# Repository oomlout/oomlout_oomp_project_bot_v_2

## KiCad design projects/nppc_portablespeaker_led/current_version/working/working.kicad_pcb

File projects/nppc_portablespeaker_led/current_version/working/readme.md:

# portablespeaker
 
## summary 
* id: nppc_portablespeaker_led
* user: nppc
* name: portablespeaker
* board: led
* repo: https://github.com/nppc/PortableSpeaker
* src_file_repo_kicad_pcb: KiCad/Led/Led.kicad_pcb
* src_file_repo_kicad_pcb_link: https://github.com/nppc/PortableSpeaker/tree/master/KiCad/Led/Led.kicad_pcb

* src_file_repo_sch: KiCad/Led/Led.sch
* src_file_repo_sch_link: https://github.com/nppc/PortableSpeaker/tree/master/KiCad/Led/Led.sch
* full details link: https://github.com/oomlout/oomlout_oomp_project_bot_v_2/tree/main/projects/nppc_portablespeaker_led/current_version/working

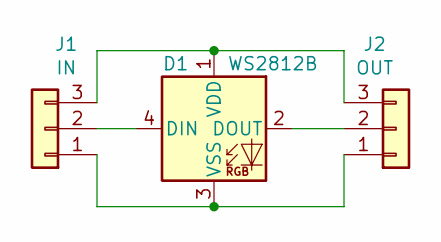
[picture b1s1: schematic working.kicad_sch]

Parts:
D1: WS2812B; LED_WS2812B_PLCC4_5.0x5.0mm_P3.2mm
J1: IN; PinHeader_1x03_P2.54mm_Vertical
J2: OUT; PinHeader_1x03_P2.54mm_Vertical

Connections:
unnamed: D1.1 (VDD), J1.3, J2.3
unnamed: D1.2 (DOUT), J2.2
unnamed: D1.3 (VSS), J1.1, J2.1
unnamed: D1.4 (DIN), J1.2

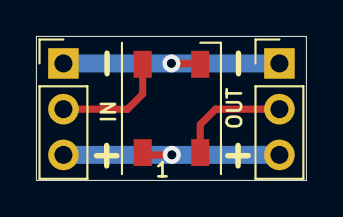
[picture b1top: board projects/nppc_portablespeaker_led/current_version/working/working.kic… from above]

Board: 2 copper layers, 15.0 x 8.0 mm, 3 parts (0 on the bottom side), 4 nets.

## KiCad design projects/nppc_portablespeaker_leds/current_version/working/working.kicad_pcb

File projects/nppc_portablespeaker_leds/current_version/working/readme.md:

# portablespeaker
 
## summary 
* id: nppc_portablespeaker_leds
* user: nppc
* name: portablespeaker
* board: leds
* repo: https://github.com/nppc/PortableSpeaker
* src_file_repo_kicad_pcb: KiCad/Leds/Leds.kicad_pcb
* src_file_repo_kicad_pcb_link: https://github.com/nppc/PortableSpeaker/tree/master/KiCad/Leds/Leds.kicad_pcb

* src_file_repo_sch: KiCad/Leds/Leds.sch
* src_file_repo_sch_link: https://github.com/nppc/PortableSpeaker/tree/master/KiCad/Leds/Leds.sch
* full details link: https://github.com/oomlout/oomlout_oomp_project_bot_v_2/tree/main/projects/nppc_portablespeaker_leds/current_version/working

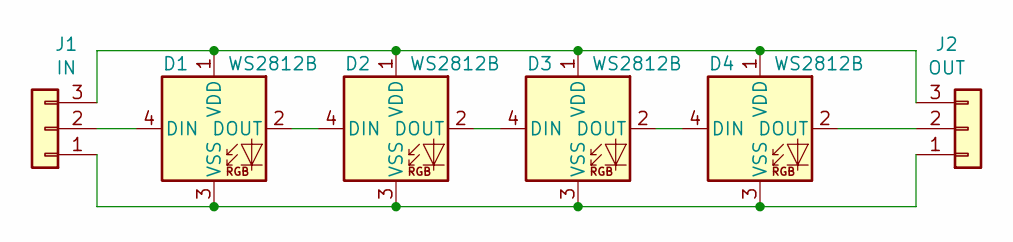
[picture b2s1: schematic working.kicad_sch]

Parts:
D1, D2, D3, D4: WS2812B; LED_WS2812B_PLCC4_5.0x5.0mm_P3.2mm
J1: IN; PinHeader_1x03_P2.54mm_Vertical
J2: OUT; PinHeader_1x03_P2.54mm_Vertical

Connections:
unnamed: D1.1 (VDD), D2.1 (VDD), D3.1 (VDD), D4.1 (VDD), J1.3, J2.3
unnamed: D1.2 (DOUT), D2.4 (DIN)
unnamed: D1.3 (VSS), D2.3 (VSS), D3.3 (VSS), D4.3 (VSS), J1.1, J2.1
unnamed: D1.4 (DIN), J1.2
unnamed: D2.2 (DOUT), D3.4 (DIN)
unnamed: D3.2 (DOUT), D4.4 (DIN)
unnamed: D4.2 (DOUT), J2.2

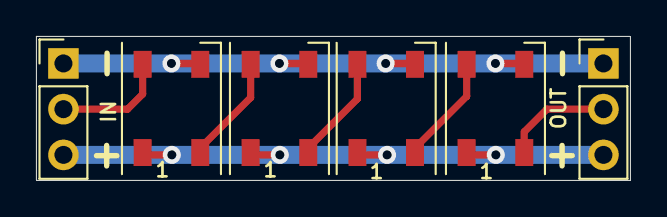
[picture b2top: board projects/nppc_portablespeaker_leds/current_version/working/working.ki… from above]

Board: 2 copper layers, 33.0 x 8.0 mm, 6 parts (0 on the bottom side), 7 nets.

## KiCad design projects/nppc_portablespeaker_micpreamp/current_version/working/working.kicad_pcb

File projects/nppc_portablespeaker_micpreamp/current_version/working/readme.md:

# portablespeaker
 
## summary 
* id: nppc_portablespeaker_micpreamp
* user: nppc
* name: portablespeaker
* board: micpreamp
* repo: https://github.com/nppc/PortableSpeaker
* src_file_repo_kicad_pcb: KiCad/MicPreamp/MicPreamp.kicad_pcb
* src_file_repo_kicad_pcb_link: https://github.com/nppc/PortableSpeaker/tree/master/KiCad/MicPreamp/MicPreamp.kicad_pcb

* src_file_repo_sch: KiCad/MicPreamp/MicPreamp.sch
* src_file_repo_sch_link: https://github.com/nppc/PortableSpeaker/tree/master/KiCad/MicPreamp/MicPreamp.sch
* full details link: https://github.com/oomlout/oomlout_oomp_project_bot_v_2/tree/main/projects/nppc_portablespeaker_micpreamp/current_version/working

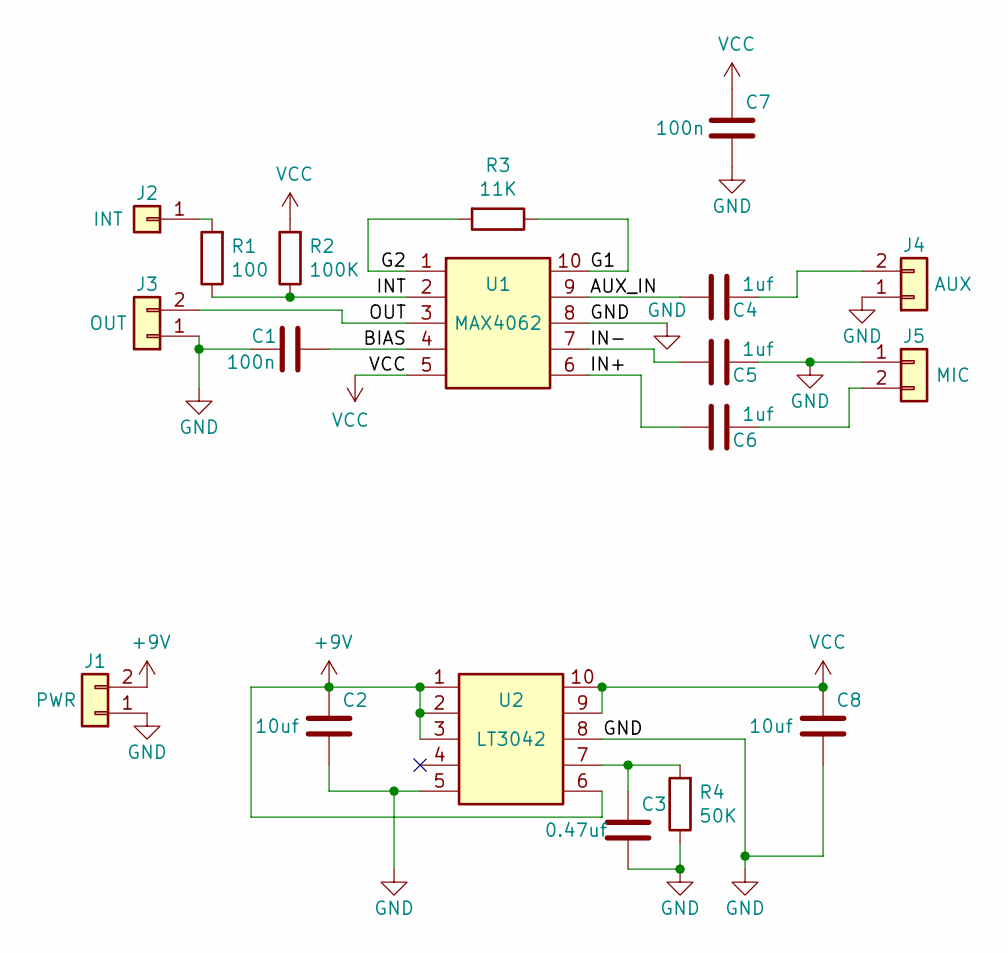
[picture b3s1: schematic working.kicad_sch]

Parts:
C1, C7: 100n; C_0603
C2, C8: 10uf; C_0603
C3: 0.47uf; C_0603
C4, C5, C6: 1uf; C_0603
J1: PWR; Conn_1x02_2.54mm
J2: INT; Conn_1x01_2.54mm
J3: OUT; Conn_1x02_2.54mm
J4: AUX; Conn_1x02_2.54mm
J5: MIC; Conn_1x02_2.54mm
R1: 100; R_0603
R2: 100K; R_0603
R3: 11K; R_0603
R4: 50K; R_0603
U1: MAX4062; TSSOP-10_3x3mm_Pitch0.5mm
U2: LT3042; MSOP-10-1EP_3x3mm_Pitch0.5mm

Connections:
+9V: C2.1, J1.2, U2.1, U2.2, U2.3, U2.6
/AUX_IN: C4.2, U1.9
/BIAS: C1.2, U1.4
/G1: R3.1, U1.10
/G2: R3.2, U1.1
/IN+: C6.2, U1.6
/IN-: C5.2, U1.7
/INT: R1.1, R2.1, U1.2
/OUT: J3.2, U1.3
GND: C1.1, C2.2, C3.2, C5.1, C7.2, C8.2, J1.1, J3.1, J4.1, J5.1, R4.1, U1.8, U2.5, U2.8, U2.11
unnamed: C3.1, R4.2, U2.7
unnamed: C4.1, J4.2
unnamed: C6.1, J5.2
unnamed: J2.1, R1.2
VCC: C7.1, C8.1, R2.2, U1.5, U2.9, U2.10

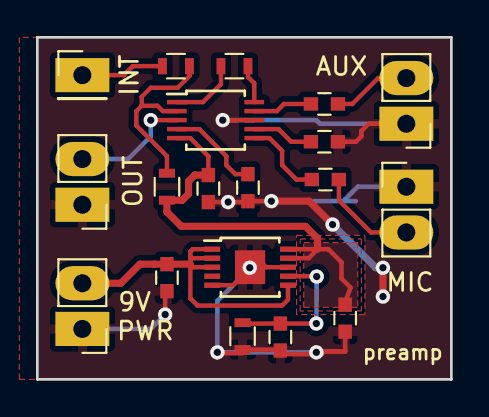
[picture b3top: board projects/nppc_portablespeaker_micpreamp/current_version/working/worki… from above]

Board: 2 copper layers, 23.0 x 19.0 mm, 19 parts (0 on the bottom side), 15 nets.

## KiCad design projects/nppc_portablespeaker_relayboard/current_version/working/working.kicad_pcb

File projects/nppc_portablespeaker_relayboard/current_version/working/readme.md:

# portablespeaker
 
## summary 
* id: nppc_portablespeaker_relayboard
* user: nppc
* name: portablespeaker
* board: relayboard
* repo: https://github.com/nppc/PortableSpeaker
* src_file_repo_kicad_pcb: KiCad/RelayBoard/RelayBoard.kicad_pcb
* src_file_repo_kicad_pcb_link: https://github.com/nppc/PortableSpeaker/tree/master/KiCad/RelayBoard/RelayBoard.kicad_pcb

* src_file_repo_sch: KiCad/RelayBoard/RelayBoard.sch
* src_file_repo_sch_link: https://github.com/nppc/PortableSpeaker/tree/master/KiCad/RelayBoard/RelayBoard.sch
* full details link: https://github.com/oomlout/oomlout_oomp_project_bot_v_2/tree/main/projects/nppc_portablespeaker_relayboard/current_version/working

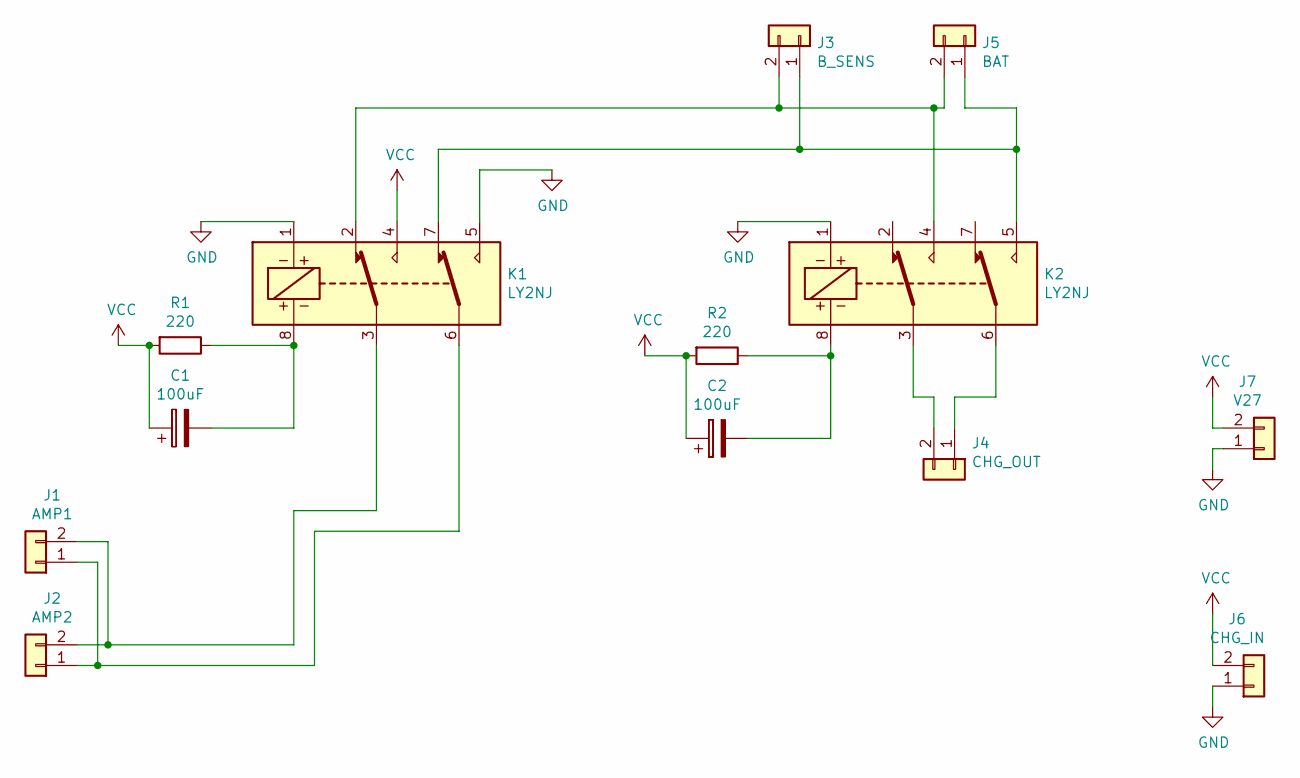
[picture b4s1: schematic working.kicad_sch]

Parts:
C1, C2: 100uF; CP_Radial_D8.0mm_P3.50mm
J1: AMP1; Conn_Power
J2: AMP2; Conn_Power
J3: B_SENS; Conn_1x02_2.54mm
J4: CHG_OUT; Conn_Power
J5: BAT; Conn_Power
J6: CHG_IN; Conn_Power
J7: V27; Conn_Power
K1, K2: LY2NJ; Relay_LY2NJ
R1, R2: 220; R_Axial_DIN0414_L11.9mm_D4.5mm_P20.32mm_Horizontal

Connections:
GND: J6.1, J7.1, K1.1, K1.5, K2.1
unnamed: C1.2, K1.8, R1.1
unnamed: C2.2, K2.8, R2.1
unnamed: J1.1, J2.1, K1.6
unnamed: J1.2, J2.2, K1.3
unnamed 5: J3.1, J5.1, K1.7, K2.5; also elsewhere on the board
unnamed 6: J3.2, J5.2, K1.2, K2.4; also elsewhere on the board
unnamed: J4.1, K2.6
unnamed: J4.2, K2.3
VCC: C1.1, C2.1, J6.2, J7.2, K1.4, R1.2, R2.2

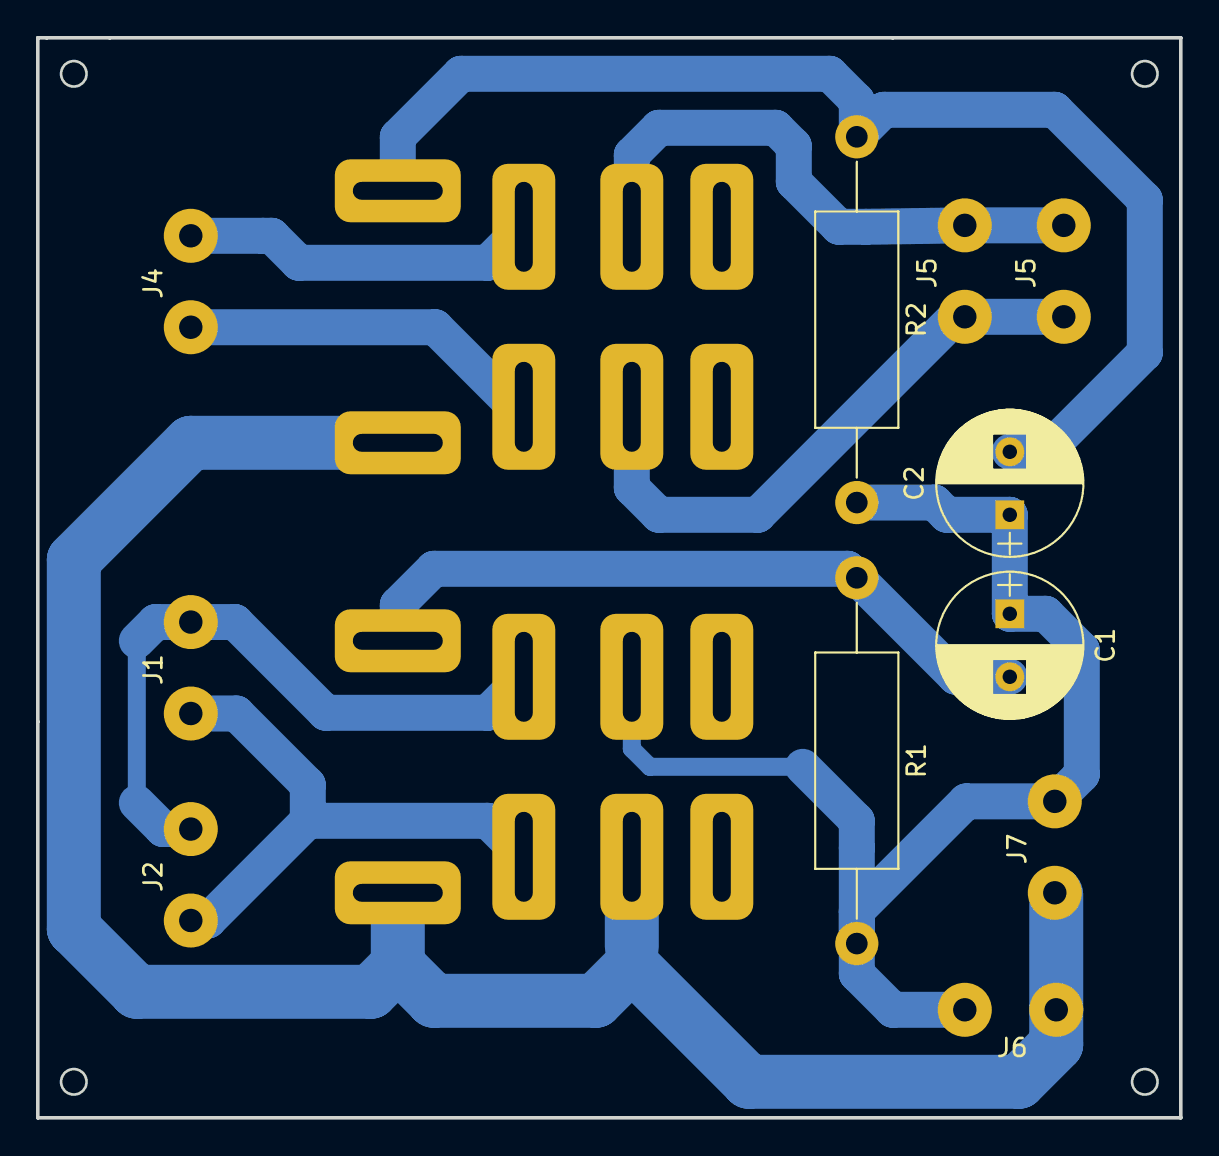
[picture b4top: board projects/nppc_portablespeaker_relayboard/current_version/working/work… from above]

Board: 2 copper layers, 63.5 x 60.0 mm, 13 parts (0 on the bottom side), 10 nets.

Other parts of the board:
J5#2: BAT; Conn_Power

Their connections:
unnamed 5: J5#2.1; also elsewhere on the board
unnamed 6: J5#2.2; also elsewhere on the board

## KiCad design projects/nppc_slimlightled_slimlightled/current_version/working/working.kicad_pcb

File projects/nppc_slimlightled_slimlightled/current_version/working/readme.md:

# slimlightled
 
## summary 
* id: nppc_slimlightled_slimlightled
* user: nppc
* name: slimlightled
* board: slimlightled
* repo: https://github.com/nppc/SlimLightLED
* src_file_repo_kicad_pcb: SlimLightLED.kicad_pcb
* src_file_repo_kicad_pcb_link: https://github.com/nppc/SlimLightLED/tree/master/SlimLightLED.kicad_pcb

* src_file_repo_sch: SlimLightLED.sch
* src_file_repo_sch_link: https://github.com/nppc/SlimLightLED/tree/master/SlimLightLED.sch
* full details link: https://github.com/oomlout/oomlout_oomp_project_bot_v_2/tree/main/projects/nppc_slimlightled_slimlightled/current_version/working

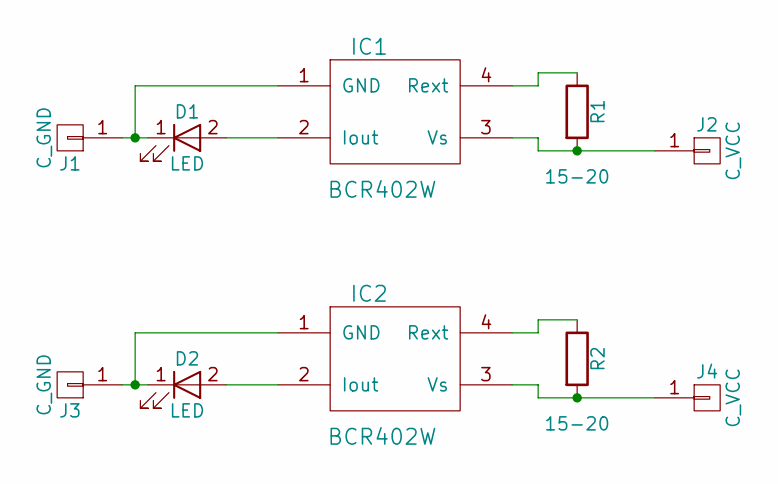
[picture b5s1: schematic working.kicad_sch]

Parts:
D1, D2: LED; 5730
IC1, IC2: BCR402W; BCR402
J1, J3: C_GND; Light_PAD
J2, J4: C_VCC; Light_PAD
R1, R2: 15-20; R_0402_NoSilk

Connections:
unnamed: D1.1 (K), IC1.1 (GND), J1.1
unnamed: D1.2 (A), IC1.2 (Iout)
unnamed: D2.1 (K), IC2.1 (GND), J3.1
unnamed: D2.2 (A), IC2.2 (Iout)
unnamed: IC1.3 (Vs), J2.1, R1.2
unnamed: IC1.4 (Rext), R1.1
unnamed: IC2.3 (Vs), J4.1, R2.2
unnamed: IC2.4 (Rext), R2.1

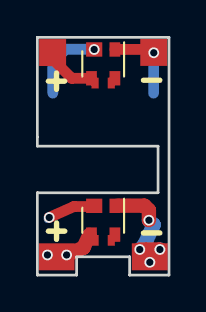
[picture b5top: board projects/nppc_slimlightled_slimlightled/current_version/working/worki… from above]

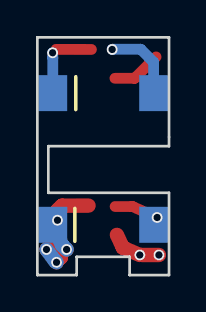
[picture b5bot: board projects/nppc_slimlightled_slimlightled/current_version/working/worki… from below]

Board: 2 copper layers, 7.3 x 13.2 mm, 10 parts (2 on the bottom side), 8 nets.

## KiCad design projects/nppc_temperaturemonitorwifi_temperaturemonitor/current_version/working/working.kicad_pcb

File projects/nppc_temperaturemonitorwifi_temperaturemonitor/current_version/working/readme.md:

# temperaturemonitorwifi
 
## summary 
* id: nppc_temperaturemonitorwifi_temperaturemonitor
* user: nppc
* name: temperaturemonitorwifi
* board: temperaturemonitor
* repo: https://github.com/nppc/TemperatureMonitorWIFI
* src_file_repo_kicad_pcb: KiCad/TemperatureMonitor.kicad_pcb
* src_file_repo_kicad_pcb_link: https://github.com/nppc/TemperatureMonitorWIFI/tree/master/KiCad/TemperatureMonitor.kicad_pcb

* src_file_repo_sch: KiCad/TemperatureMonitor.sch
* src_file_repo_sch_link: https://github.com/nppc/TemperatureMonitorWIFI/tree/master/KiCad/TemperatureMonitor.sch
* full details link: https://github.com/oomlout/oomlout_oomp_project_bot_v_2/tree/main/projects/nppc_temperaturemonitorwifi_temperaturemonitor/current_version/working

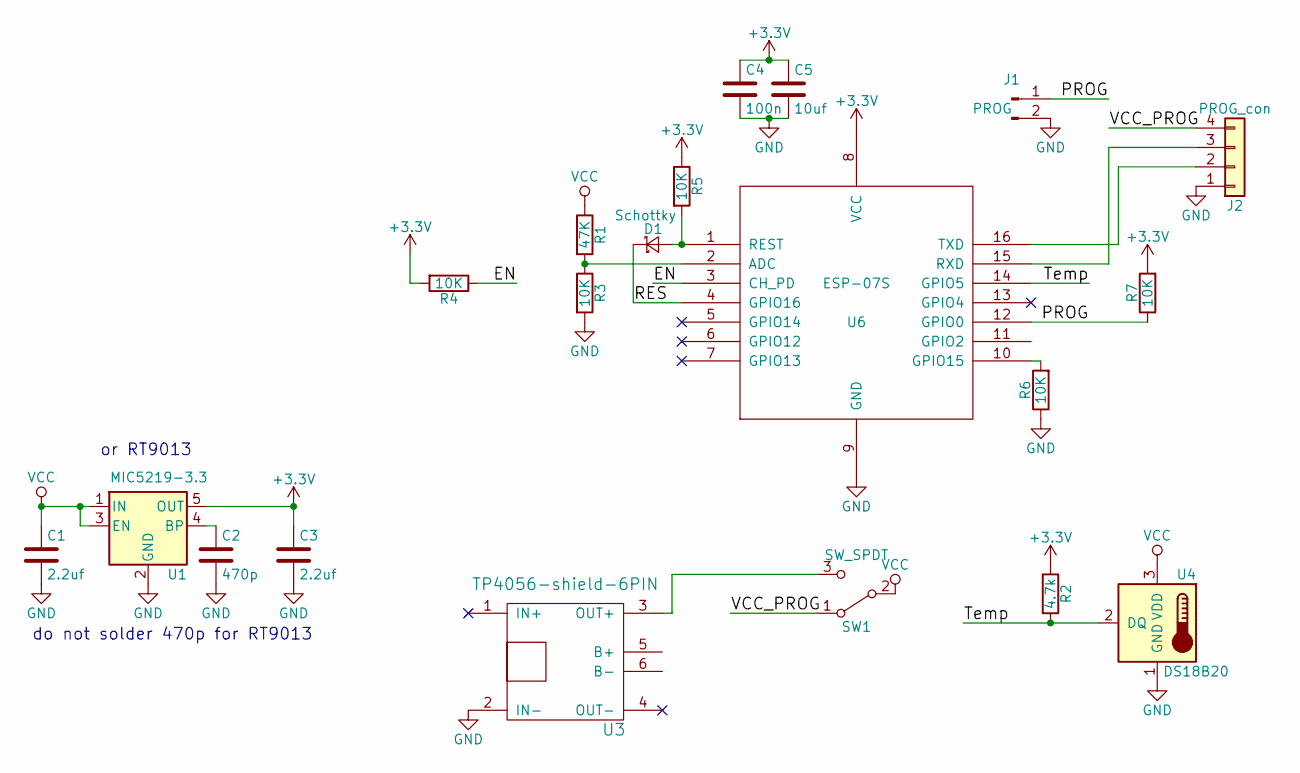
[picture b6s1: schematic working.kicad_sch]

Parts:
C1, C3: 2.2uf; C_0805
C2: 470p; C_0603
C4: 100n; C_0603
C5: 10uf; C_0805
D1: Schottky; D_SOD-523
J1: PROG; Pin_Header_Straight_1x02_Pitch2.54mm
J2: PROG_con; Pin_Header_Straight_1x04_Pitch2.54mm
R1: 47K; R_0603
R2: 4.7k; R_0603
R3, R4, R5, R6, R7: 10K; R_0603
SW1: SW_SPDT; SK12D07VG3
U1: MIC5219-3.3; SOT-23-5
U3: TP4056-shield-6PIN
U4: DS18B20; TO-92_Inline_Narrow_Oval
U6: ESP-07S

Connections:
+3V3: C3.1, C4.1, C5.1, R2.1, R4.2, R5.1, R7.2, U1.5 (OUT), U6.8 (VCC)
/EN: R4.1, U6.3 (CH_PD)
/PROG: J1.1, R7.1, U6.12 (GPIO0)
/RES: D1.1 (K), U6.4 (GPIO16)
/Temp: R2.2, U4.2 (DQ), U6.14 (GPIO5)
/VCC_PROG: J2.4, SW1.1 (A)
GND: C1.2, C2.2, C3.2, C4.2, C5.2, J1.2, J2.1, R3.2, R6.1, U1.2 (GND), U3.2 (IN-), U4.1 (GND), U6.9 (GND)
unnamed: C2.1, U1.4 (BP)
unnamed: D1.2 (A), R5.2, U6.1 (REST)
unnamed: J2.2, U6.16 (TXD)
unnamed: J2.3, U6.15 (RXD)
unnamed: R1.2, R3.1, U6.2 (ADC)
unnamed: R6.2, U6.10 (GPIO15)
unnamed: SW1.3 (C), U3.3 (OUT+)
VCC: C1.1, R1.1, SW1.2 (B), U1.1 (IN), U1.3 (EN), U4.3 (VDD)

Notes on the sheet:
do not solder 470p for RT9013
or RT9013

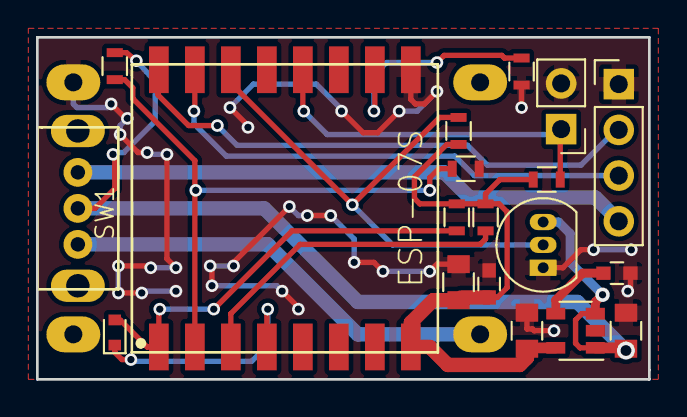
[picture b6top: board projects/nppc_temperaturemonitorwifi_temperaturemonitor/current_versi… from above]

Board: 2 copper layers, 34.0 x 19.0 mm, 20 parts (1 on the bottom side), 15 nets.

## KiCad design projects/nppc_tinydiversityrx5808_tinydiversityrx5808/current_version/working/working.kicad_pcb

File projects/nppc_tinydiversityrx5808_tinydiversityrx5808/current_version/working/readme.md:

# tinydiversityrx5808
 
## summary 
* id: nppc_tinydiversityrx5808_tinydiversityrx5808
* user: nppc
* name: tinydiversityrx5808
* board: tinydiversityrx5808
* repo: https://github.com/nppc/TinyDiversityRX5808
* src_file_repo_kicad_pcb: KiCad/TinyDiversityRX5808.kicad_pcb
* src_file_repo_kicad_pcb_link: https://github.com/nppc/TinyDiversityRX5808/tree/master/KiCad/TinyDiversityRX5808.kicad_pcb

* src_file_repo_sch: KiCad/TinyDiversityRX5808.sch
* src_file_repo_sch_link: https://github.com/nppc/TinyDiversityRX5808/tree/master/KiCad/TinyDiversityRX5808.sch
* full details link: https://github.com/oomlout/oomlout_oomp_project_bot_v_2/tree/main/projects/nppc_tinydiversityrx5808_tinydiversityrx5808/current_version/working

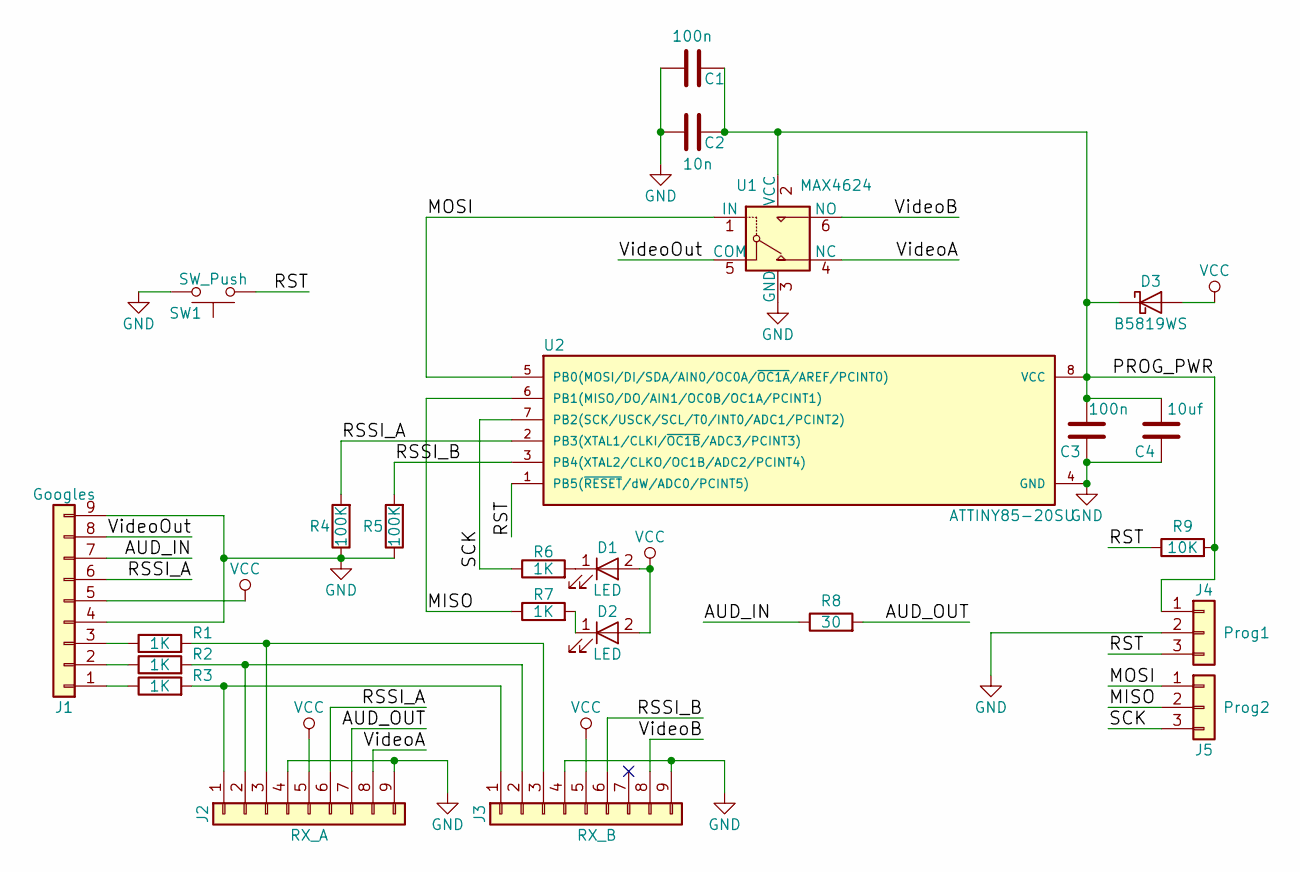
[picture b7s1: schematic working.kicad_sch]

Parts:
C1, C3: 100n; C_0603
C2: 10n; C_0603
C4: 10uf; C_0603
D1, D2: LED; LED_0805
D3: B5819WS; D_SOD-323
J1: Googles; Molex_PicoBlade_53047-0910_09x1.25mm_Straight
J2: RX_A; Molex_PicoBlade_53048-0910_09x1.25mm_Angled
J3: RX_B; Molex_PicoBlade_53048-0910_09x1.25mm_Angled
J4: Prog1; Pads_prog_3pin1.25mm
J5: Prog2; Pads_prog_3pin1.25mm
R1, R2, R3, R6, R7: 1K; R_0603
R4, R5: 100K; R_0603
R8: 30; R_0603
R9: 10K; R_0603
SW1: SW_Push; Button_TS-018
U1: MAX4624; SOT-23-6
U2: ATTINY85-20SU; SOIJ-8_5.3x5.3mm_Pitch1.27mm

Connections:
/AUD_IN: J1.7, R8.1
/AUD_OUT: J2.7, R8.2
/MISO: J5.2, R7.1, U2.6 (PB1(MISO/DO/AIN1/OC0B/OC1A/PCINT1))
/MOSI: J5.1, U1.1 (IN), U2.5 (PB0(MOSI/DI/SDA/AIN0/OC0A/~OC1A/AREF/PC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)
/PROG_PWR: C1.1, C2.1, C3.2, C4.2, D3.1 (K), J4.1, R9.2, U1.2 (VCC), U2.8 (VCC)
/RSSI_A: J1.6, J2.6, R4.2, U2.2 (PB3(XTAL1/CLKI/~OC1B/ADC3/PCINT3))
/RSSI_B: J3.6, R5.2, U2.3 (PB4(XTAL2/CLKO/OC1B/ADC2/PCINT4))
/RST: J4.3, R9.1, SW1.1, U2.1 (PB5(~RESET/dW/ADC0/PCINT5))
/SCK: J5.3, R6.1, U2.7 (PB2(SCK/USCK/SCL/T0/INT0/ADC1/PCINT2))
/VideoA: J2.8, U1.4 (NC)
/VideoB: J3.8, U1.6 (NO)
/VideoOut: J1.8, U1.5 (COM)
GND: C1.2, C2.2, C3.1, C4.1, J1.4, J1.9, J2.4, J2.9, J3.4, J3.9, J4.2, R4.1, R5.1, SW1.2, U1.3 (GND), U2.4 (GND)
unnamed 13: D1.1 (K), R6.2; also elsewhere on the board
unnamed 14: D2.1 (K), R7.2; also elsewhere on the board
unnamed: J1.1, R3.1
unnamed: J1.2, R2.1
unnamed: J1.3, R1.1
unnamed: J2.1, J3.1, R3.2
unnamed: J2.2, J3.2, R2.2
unnamed: J2.3, J3.3, R1.2
VCC: D1.2 (A), D2.2 (A), D3.2 (A), J1.5, J2.5, J3.5; also elsewhere on the board

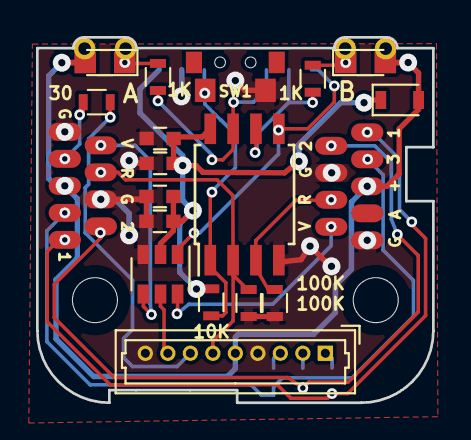
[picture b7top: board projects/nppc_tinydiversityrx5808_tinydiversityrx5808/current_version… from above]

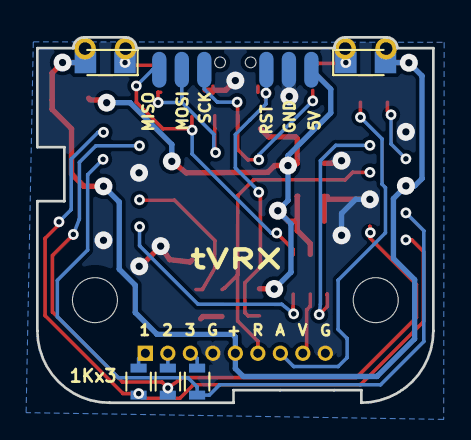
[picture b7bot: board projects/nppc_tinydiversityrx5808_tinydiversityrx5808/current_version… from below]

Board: 2 copper layers, 22.0 x 20.3 mm, 26 parts (7 on the bottom side), 22 nets.

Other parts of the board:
D1#2, D2#2: LED; LED_0805

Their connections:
unnamed 13: D1#2.1; also elsewhere on the board
unnamed 14: D2#2.1; also elsewhere on the board
VCC: D1#2.2, D2#2.2; also elsewhere on the board
